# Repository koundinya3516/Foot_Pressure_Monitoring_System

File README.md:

# Foot_Pressure_Monitoring_System
new repo

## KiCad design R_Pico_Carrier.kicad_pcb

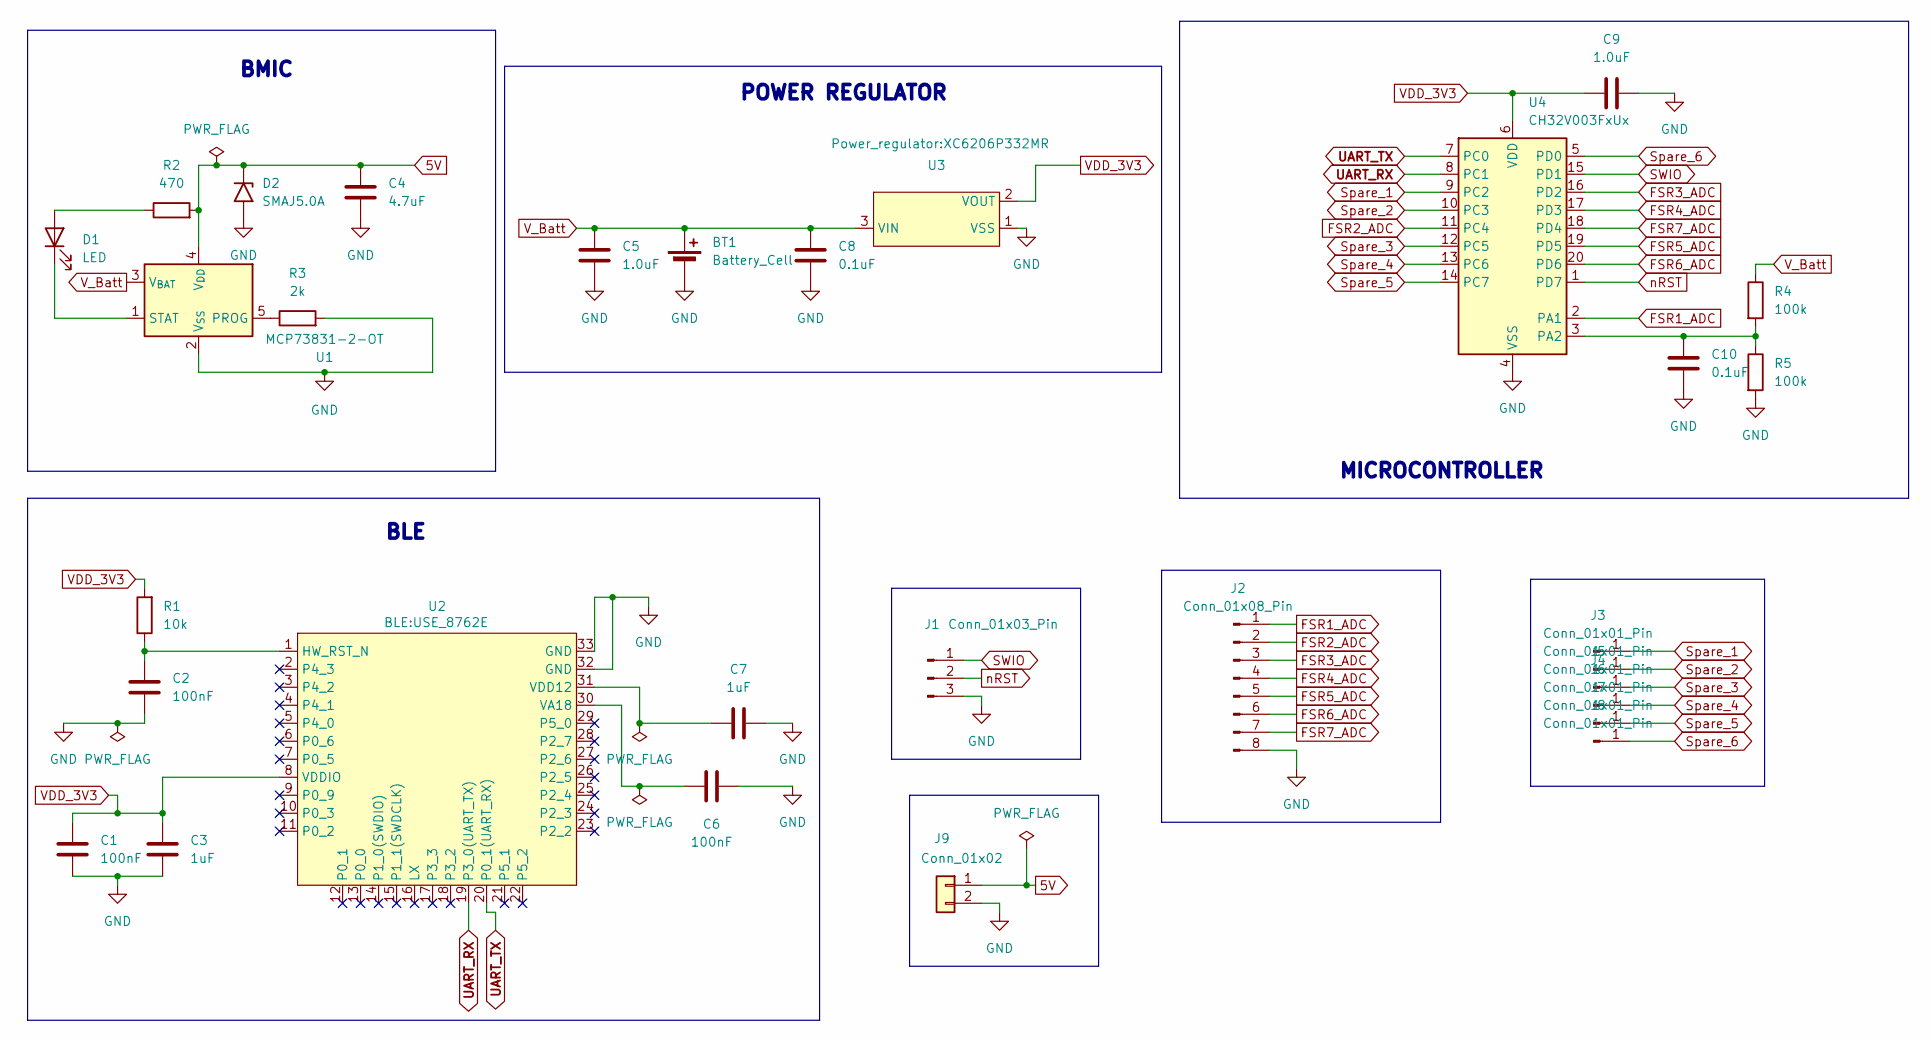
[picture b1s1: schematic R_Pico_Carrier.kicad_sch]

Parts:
BT1: Battery_Cell; PinHeader_1x02_P2.54mm_Vertical
C1, C2, C6: 100nF; C_0603_1608Metric
C3, C7: 1uF; C_0603_1608Metric
C4: 4.7uF; C_0603_1608Metric
C5, C9: 1.0uF; C_0603_1608Metric
C8, C10: 0.1uF; C_0603_1608Metric
D1: LED; LED_0603_1608Metric
D2: SMAJ5.0A; D_SMA
J1: Conn_01x03_Pin; PinHeader_1x03_P2.54mm_Vertical
J2: Conn_01x08_Pin; PinHeader_1x08_P2.54mm_Vertical
J3, J4, J5, J6, J7, J8: Conn_01x01_Pin; TestPoint_Pad_D1.5mm
J9: Conn_01x02; PinHeader_1x02_P2.54mm_Vertical
R1: 10k; R_0603_1608Metric
R2: 470; R_0603_1608Metric
R3: 2k; R_0603_1608Metric
R4, R5: 100k; R_0603_1608Metric
U1: MCP73831-2-OT; SOT-23-5
U2: USE_8762E
U3: XC6206P332MR
U4: CH32V003FxUx; QFN-20-1EP_3x3mm_P0.4mm_EP1.65x1.65mm

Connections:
5V: C4.1, D2.1 (A1), J9.1, R2.2, U1.4 (V_{DD})
FSR1_ADC: J2.1, U4.2 (PA1)
FSR2_ADC: J2.2, U4.11 (PC4)
FSR3_ADC: J2.3, U4.16 (PD2)
FSR4_ADC: J2.4, U4.17 (PD3)
FSR5_ADC: J2.5, U4.19 (PD5)
FSR6_ADC: J2.6, U4.20 (PD6)
FSR7_ADC: J2.7, U4.18 (PD4)
GND: BT1.2 (-), C1.2, C2.2, C3.2, C4.2, C5.2, C6.2, C7.2, C8.2, C9.2, C10.2, D2.2 (A2), J1.3, J2.8, J9.2, R3.2, R5.2, U1.2 (V_{SS}), U2.32 (GND), U2.33 (GND), U3.1 (VSS), U4.4 (VSS), U4.21 (VSS)
unnamed: D1.2 (A), R2.1
unnamed: D1.1 (K), U1.1 (STAT)
unnamed: R3.1, U1.5 (PROG)
unnamed: C2.1, R1.1, U2.1 (HW_RST_N)
unnamed: C6.1, U2.30 (VA18)
unnamed: C7.1, U2.31 (VDD12)
unnamed: C10.1, R4.2, R5.1, U4.3 (PA2)
SWIO: J1.1, U4.15 (PD1)
Spare_1: J3.1, U4.9 (PC2)
Spare_2: J4.1, U4.10 (PC3)
Spare_3: J5.1, U4.12 (PC5)
Spare_4: J6.1, U4.13 (PC6)
Spare_5: J7.1, U4.14 (PC7)
Spare_6: J8.1, U4.5 (PD0)
UART_RX: U2.19 (P3_0(UART_TX)), U4.8 (PC1)
UART_TX: U2.20 (P0_1(UART_RX)), U4.7 (PC0)
VDD_3V3: C1.1, C3.1, C9.1, R1.2, U2.8 (VDDIO), U3.2 (VOUT), U4.6 (VDD)
V_Batt: BT1.1 (+), C5.1, C8.1, R4.1, U1.3 (V_{BAT}), U3.3 (VIN)
nRST: J1.2, U4.1 (PD7)

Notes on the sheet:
^{BMIC}
^{MICROCONTROLLER}
^{POWER REGULATOR}
^{BLE}

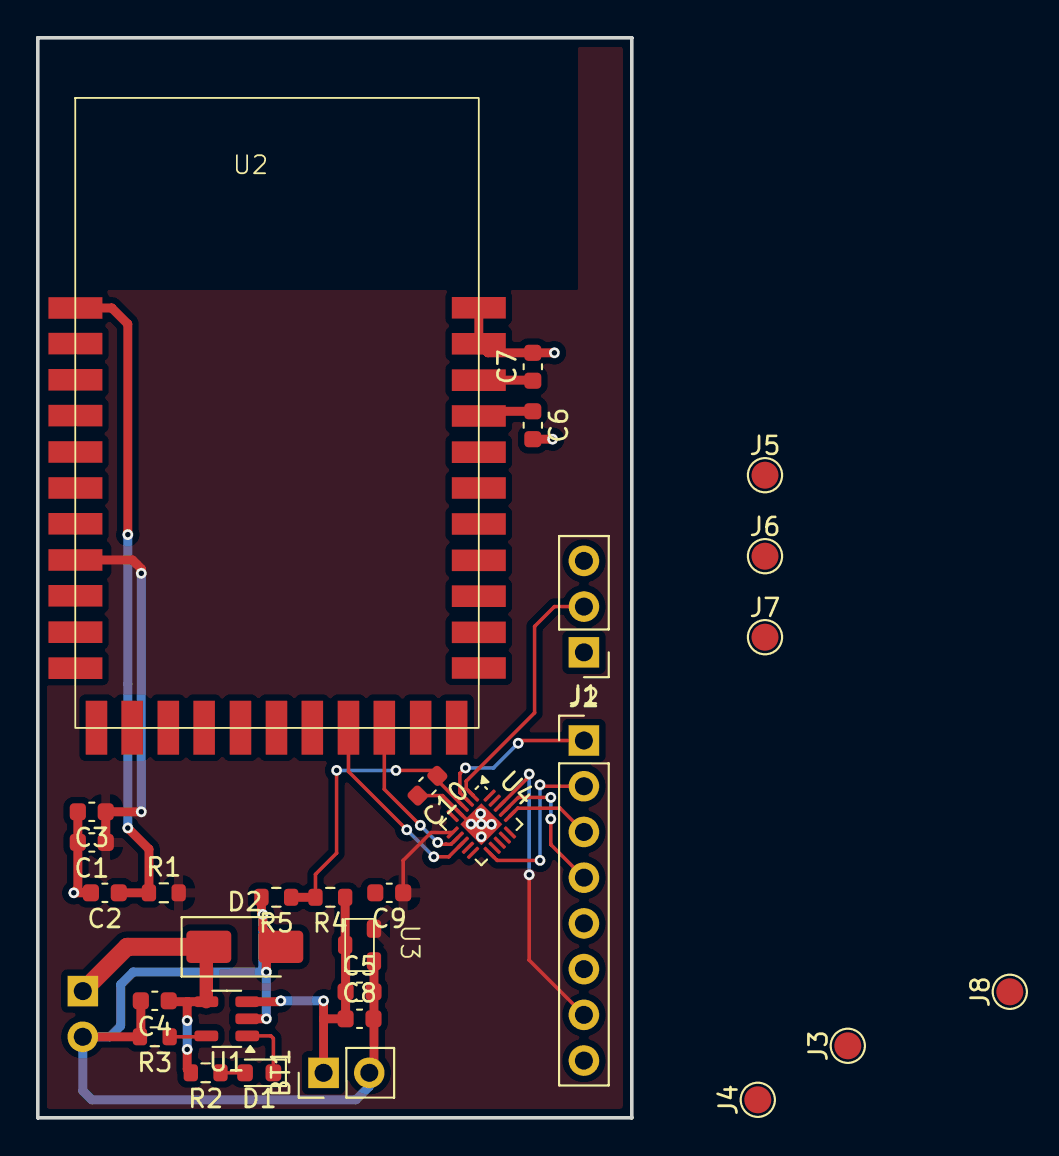
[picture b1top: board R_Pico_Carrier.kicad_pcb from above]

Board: 2 copper layers, 33.0 x 60.0 mm, 31 parts (1 on the bottom side), 28 nets.

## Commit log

2025-08-31 Re-do the board for smaller and tidy palcement
